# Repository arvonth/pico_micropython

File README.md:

# pico_micropython
Various Raspberry Pi Pico micropython projects

### air_qual_disp
Display information from an ENS160 Digital Metal-Oxide (MOX) Multi-Gas Sensor on a SSD1306 based OLED display.  Uses code from https://github.com/CoreElectronics

### air_qual_mqtt
Display information from an ENS160 Digital Metal-Oxide (MOX) Multi-Gas Sensor on a SSD1306 based OLED display and publish to MQTT topics. Uses code from https://github.com/CoreElectronics 

### bw_air_qual
Scroll a logo on a SSD1306 based OLED display and display information from an EN160 sensor.

### bw_scroll
Scroll a logo on a SSD1306 based OLED display.

### ens160
Display information from an ENS160 Digital Metal-Oxide (MOX) Multi-Gas Sensor.  Code copied from https://core-electronics.com.au/guides/piicodev-air-quality-sensor-ens160-getting-started-guide/ and uses code from https://github.com/CoreElectronics

### mqtt_example
Pico W MQTT example based on Les Pounder's article on Tom's Hardware https://www.tomshardware.com/how-to/send-and-receive-data-raspberry-pi-pico-w-mqtt

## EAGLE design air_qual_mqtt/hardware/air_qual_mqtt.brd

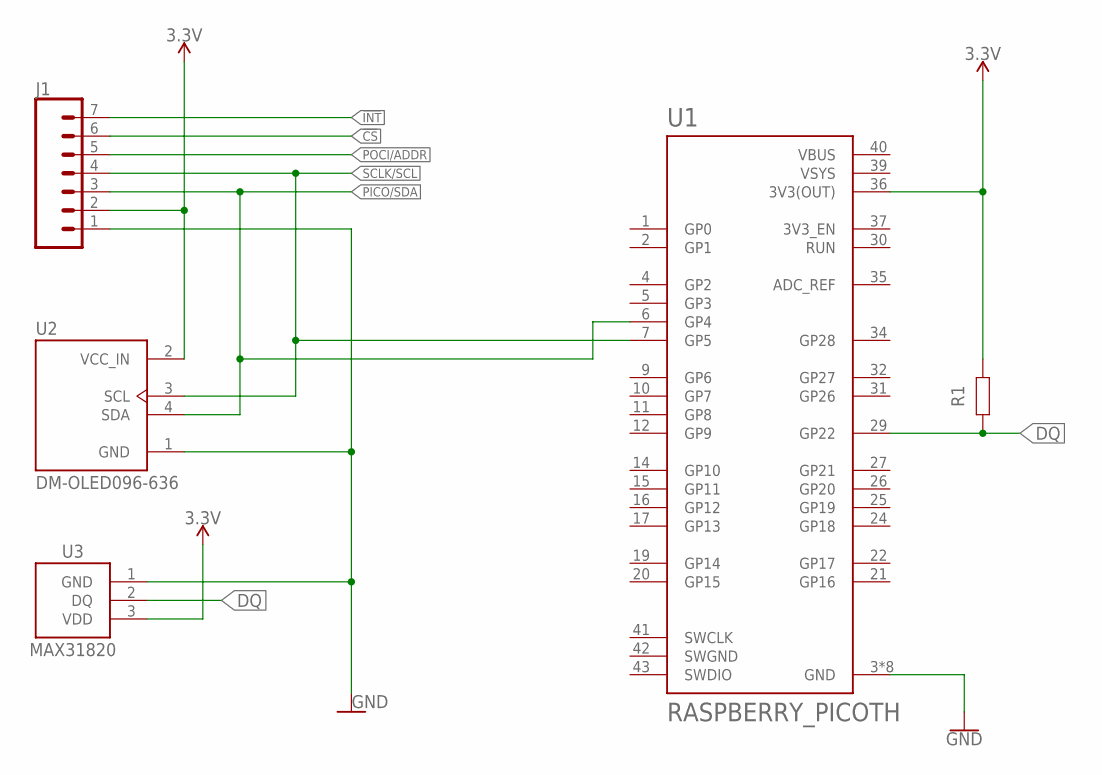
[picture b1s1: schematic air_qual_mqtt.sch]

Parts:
J1: CONN_07NO_SILK; 1X07_NO_SILK
R1: R_AXIAL-11.7MM-PITCH; RESAD1176W63L850D250B
U1: RASPBERRY_PICOTH; PICO-PKG-TH
U2: DM-OLED096-636; MODULE_DM-OLED096-636
U3: MAX31820; TO92

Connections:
3.3V: J1.2, R1.2, U1.36 (3V3(OUT)), U2.2 (VCC_IN), U3.3 (VDD)
!CS!: J1.6
!INT!: J1.7
DQ: R1.1, U1.29 (GP22), U3.2 (DQ)
GND: J1.1, U1.3 (GND), U1.8 (GND), U1.13 (GND), U1.18 (GND), U1.23 (GND), U1.28 (GND), U1.33 (GND), U1.38 (GND), U2.1 (GND), U3.1 (GND)
PICO/SDA: J1.3, U1.6 (GP4), U2.4 (SDA)
POCI/ADDR: J1.5
SCLK/SCL: J1.4, U1.7 (GP5), U2.3 (SCL)
SWGND: U1.42 (SWGND)
VBUS: U1.40 (VBUS)
VSYS: U1.39 (VSYS)

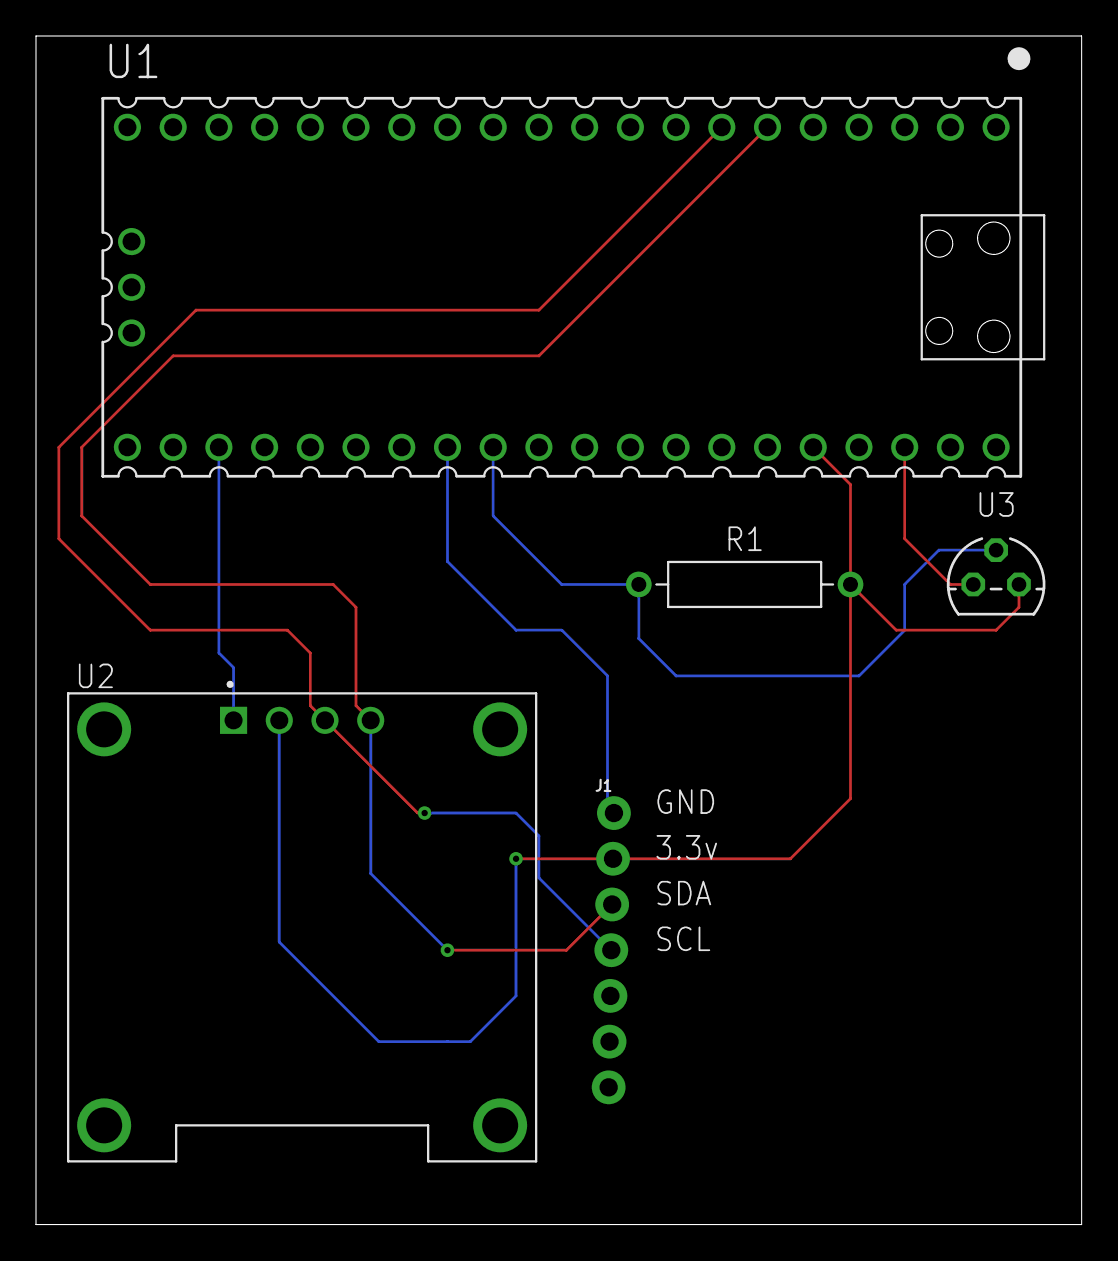
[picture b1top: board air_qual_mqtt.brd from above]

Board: 2 copper layers, 58.1 x 66.0 mm, 5 parts (0 on the bottom side), 5 nets.

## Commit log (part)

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2023-05-31 add new project and refactor air_qual_disp code
2023-06-01 add blit calls to air_qual_diso
2023-06-02 add blank blits before reporting sensor mode
2023-06-12 add air_qual_mqtt project
2023-06-12 add basic functionality to air_qual_mqtt
2023-06-12 1st working version
2023-06-22 blank the whole top line of text on ssd1306 display
2023-08-29 change mqtt broker and add authentication to the connection
2024-09-02 display init status on oled
2025-02-25 Update blanking byte array. Add wait to ensure Wi-Fi connection.
2025-05-10 add ds18b20 sensor and refactor using ChatGPT
2025-05-13 Add schematic and PCB file for the air quality monitor project
2025-05-27 Add animations to air_qual_mqtt project. Add mqtt subscribe example

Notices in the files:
parts and their libraries:
SparkFun-Connectors: Licensing: Creative Commons ShareAlike 4.0 International - https://creativecommons.org/licenses/by-sa/4.0
